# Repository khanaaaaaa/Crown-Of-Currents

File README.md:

Zine:

# What It Is and Why I Made It

A custom shaped PCB designed to look like a crown with 12 LEDs with a USB A connector at the bottom. If you plug it to a power source and switch it on, it lights up all at once. Quite simple project as I am a beginner and wanted to make something similar to:
https://www.instagram.com/p/DPHaJFgCGyA/
But couldn't figure it out so went for a simpler goal.

# How You Use It

1. Plug in a USB Type-A cable into the J1 connector
2. Flip SW1 on the ON position
3. All 12 LEDs should light up.

Bill of Materials in CSV:
[crown_led_pcb_bom.csv](https://github.com/user-attachments/files/26826730/crown_led_pcb_bom.csv)

## Bill of Materials

| Reference | Component | Description | Qty | Manufacturer | Mfr Part # | Supplier | Supplier Part # | Unit Price | Extended Price |
|-----------|-----------|-------------|:---:|--------------|------------|----------|----------------|----------:|---------------:|
| D1–D12 | 5mm Red LED | Through-hole red LED 5mm | 12 | Kingbright | WP7113ID | [LCSC](https://www.lcsc.com/product-detail/C2296.html) | C2296 | $0.05 | $0.60 |
| J1 | USB Type-A Connector | USB Type-A female power input | 1 | Amphenol | 787480-1 | [LCSC](https://www.lcsc.com/product-detail/C46407.html) | C46407 | $0.15 | $0.15 |
| R1 | Resistor 150Ω | Current limiting resistor 1/4W | 1 | Yageo | CFR-25JB-52-150R | [LCSC](https://www.lcsc.com/product-detail/C114688.html) | C114688 | $0.01 | $0.01 |
| SW1 | Slide Switch | SPDT slide switch power on/off | 1 | C&K | OS102011MS2QN1 | [LCSC](https://www.lcsc.com/product-detail/C128955.html) | C128955 | $0.10 | $0.10 |

**Total: $0.86** · All parts available at [LCSC](https://lcsc.com)

JLCPCB:

Schematic:

PCB:

3D View:

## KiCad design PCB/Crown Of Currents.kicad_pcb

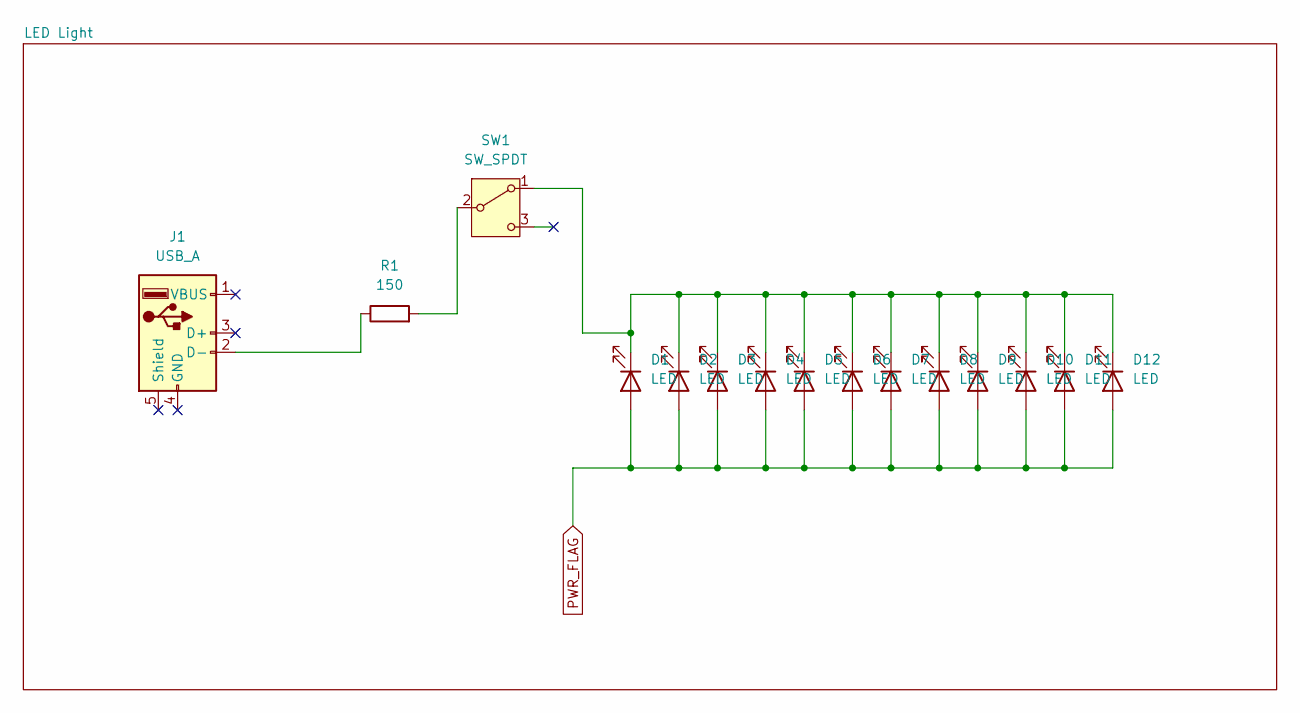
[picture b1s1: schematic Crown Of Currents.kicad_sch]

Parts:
D1, D2, D3, D4, D5, D6, D7, D8, D9, D10, D11, D12: LED; LED_D5.0mm
J1: USB_A; USB_A_Molex_67643_Horizontal
R1: 150; R_Axial_DIN0204_L3.6mm_D1.6mm_P5.08mm_Horizontal
SW1: SW_SPDT; SW_CK_JS202011AQN_DPDT_Angled

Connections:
unnamed: D1.1 (K), D2.1 (K), D3.1 (K), D4.1 (K), D5.1 (K), D6.1 (K), D7.1 (K), D8.1 (K), D9.1 (K), D10.1 (K), D11.1 (K), D12.1 (K), SW1.1 (A)
unnamed: J1.2 (D-), R1.1
unnamed: R1.2, SW1.2 (B)
PWR_FLAG: D1.2 (A), D2.2 (A), D3.2 (A), D4.2 (A), D5.2 (A), D6.2 (A), D7.2 (A), D8.2 (A), D9.2 (A), D10.2 (A), D11.2 (A), D12.2 (A)

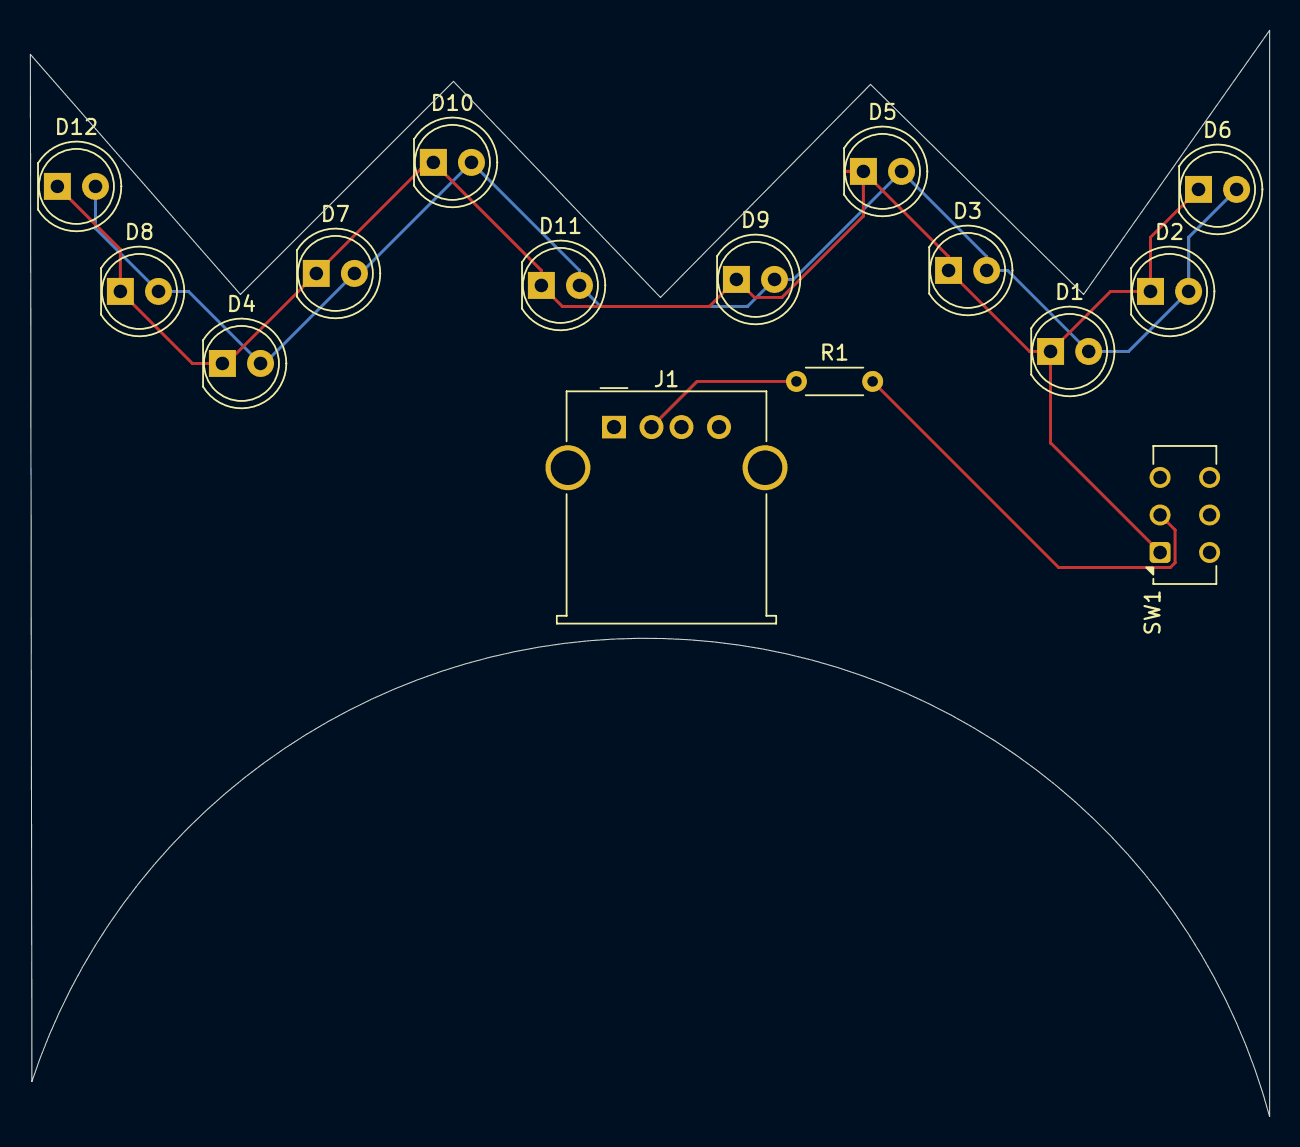
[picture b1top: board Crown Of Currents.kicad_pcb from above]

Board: 2 copper layers, 82.6 x 72.4 mm, 15 parts (0 on the bottom side), 4 nets.

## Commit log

2026-04-14 Added the required files
2026-04-17 Update README with the schematic and PCB
2026-04-17 Finished README
2026-04-17 Uploaded BOM
2026-04-17 The previous BOM wasn't loading
2026-04-17 Revise Bill of Materials to table format
    Updated the Bill of Materials section to use a table format for better readability.
2026-04-17 Remove PCB entry from parts list
    Removed the entry for the custom green PCB from the parts list.
2026-04-17 Fix spelling in README
    Corrected spelling of 'switch'
2026-04-17 Added BOM in Repsitory
2026-05-08 Enhance Bill of Materials with links and formatting
    Updated Bill of Materials table with links and formatting.
2026-05-10 Organized the folders
2026-05-10 Added a different BOM link
2026-05-10 Added zine png
2026-05-11 Added the pdf format
2026-05-11 Testing pdf
